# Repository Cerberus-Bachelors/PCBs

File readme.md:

# Interface PCBs 

This repository contains the schematics and pcb designs for the PSU interface and the sensor board interface.

## Buck Boost Interface

This interface adds connectors for buck and boost converters for ease of use.

Buck converter used: LM2596S

Boost converter used: XL6009E1

## Sensor Mount

This interface add connectors for sensor boards, esp and external sensors for ease of use.

IMU Used: Sparkfun ISM330DHCX with MMC5983MA 9Dof board

GNSS Used: NEO-M9N Sparkfun board

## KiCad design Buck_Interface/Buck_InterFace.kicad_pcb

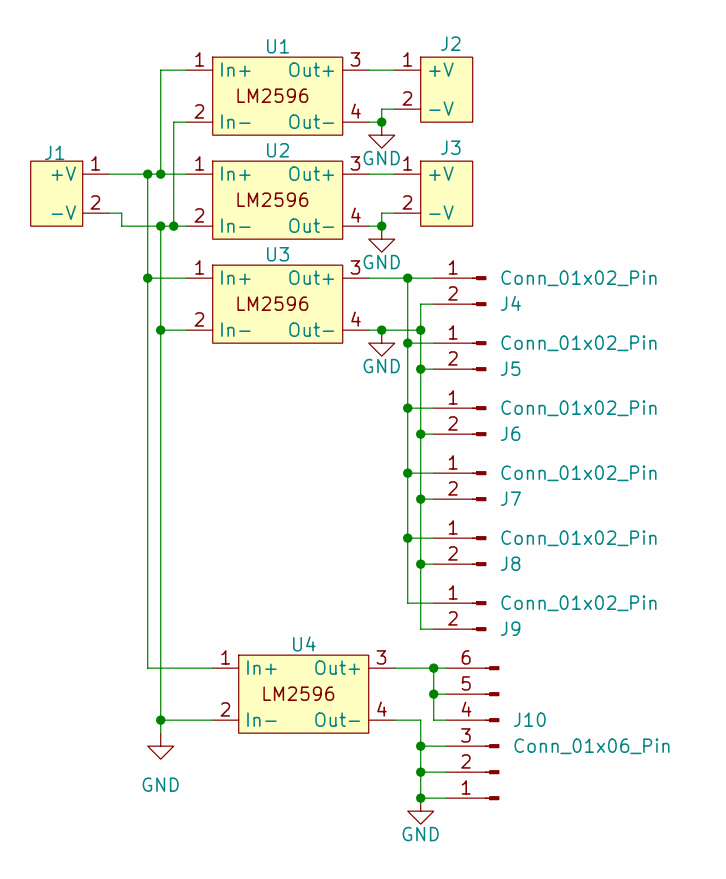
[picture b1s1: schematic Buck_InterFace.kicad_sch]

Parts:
J1, J2, J3: XT30
J4, J5, J6, J7, J8, J9: Conn_01x02_Pin; PinHeader_1x02_P2.54mm_Vertical
J10: Conn_01x06_Pin; PinSocket_1x06_P2.54mm_Vertical
U1, U2, U3, U4: Buck

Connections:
GND: J1.2 (-V), J2.2 (-V), J3.2 (-V), J4.2, J5.2, J6.2, J7.2, J8.2, J9.2, J10.1, J10.2, J10.3, U1.2 (In-), U1.4 (Out-), U2.2 (In-), U2.4 (Out-), U3.2 (In-), U3.4 (Out-), U4.2 (In-), U4.4 (Out-)
unnamed: J1.1 (+V), U1.1 (In+), U2.1 (In+), U3.1 (In+), U4.1 (In+)
unnamed: J2.1 (+V), U1.3 (Out+)
unnamed: J3.1 (+V), U2.3 (Out+)
unnamed: J4.1, J5.1, J6.1, J7.1, J8.1, J9.1, U3.3 (Out+)
unnamed: J10.4, J10.5, J10.6, U4.3 (Out+)

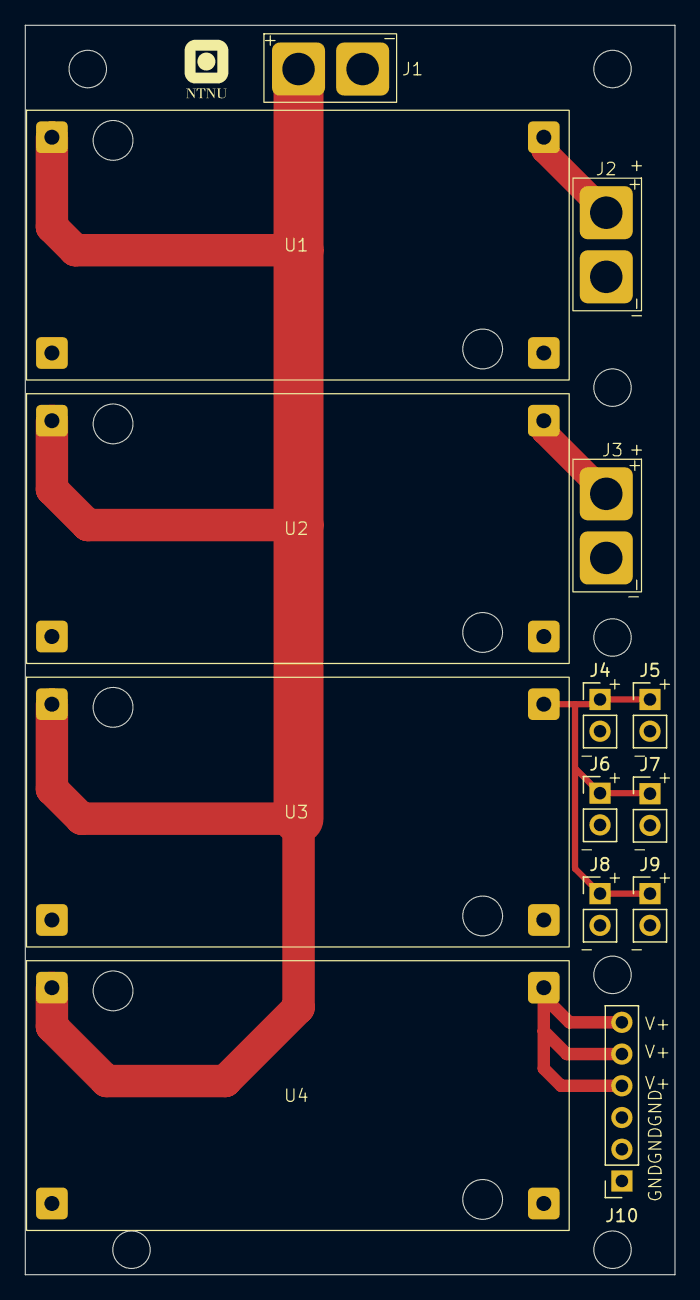
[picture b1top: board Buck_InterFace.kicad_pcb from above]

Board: 2 copper layers, 52.0 x 100.0 mm, 14 parts (0 on the bottom side), 6 nets.

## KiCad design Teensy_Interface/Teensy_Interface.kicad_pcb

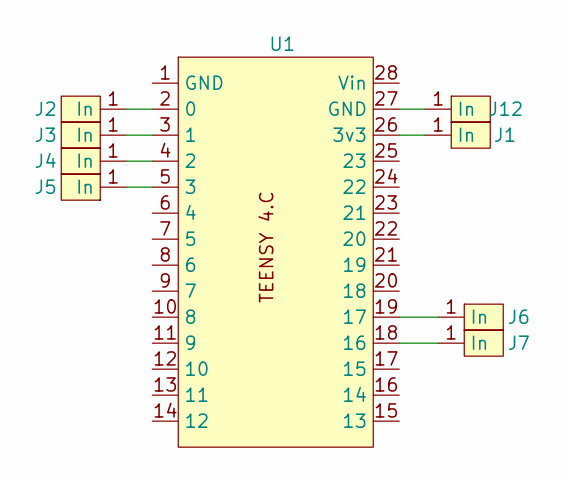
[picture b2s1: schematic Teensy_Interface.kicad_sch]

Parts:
J1, J2, J3, J4, J5, J6, J7, J12: Lug_Terminal
U1: Teensy_14pin

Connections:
unnamed: J1.1 (In), U1.26 (3v3)
unnamed: J2.1 (In), U1.2 (0)
unnamed: J3.1 (In), U1.3 (1)
unnamed: J4.1 (In), U1.4 (2)
unnamed: J5.1 (In), U1.5 (3)
unnamed: J6.1 (In), U1.19 (17)
unnamed: J7.1 (In), U1.18 (16)
unnamed: J12.1 (In), U1.27 (GND)

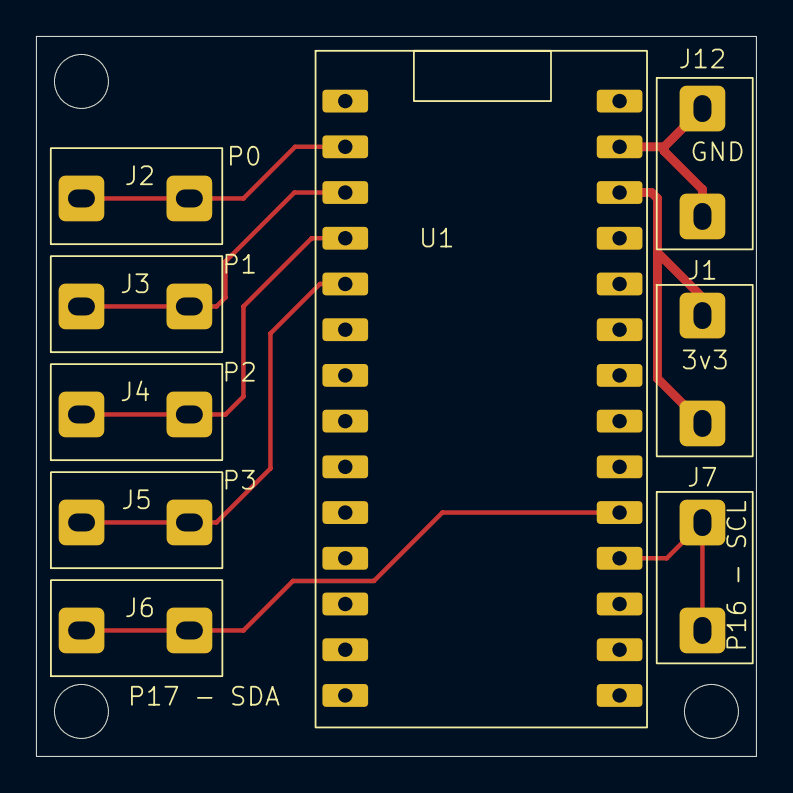
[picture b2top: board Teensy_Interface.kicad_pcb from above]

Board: 2 copper layers, 40.0 x 40.0 mm, 9 parts (0 on the bottom side), 8 nets.

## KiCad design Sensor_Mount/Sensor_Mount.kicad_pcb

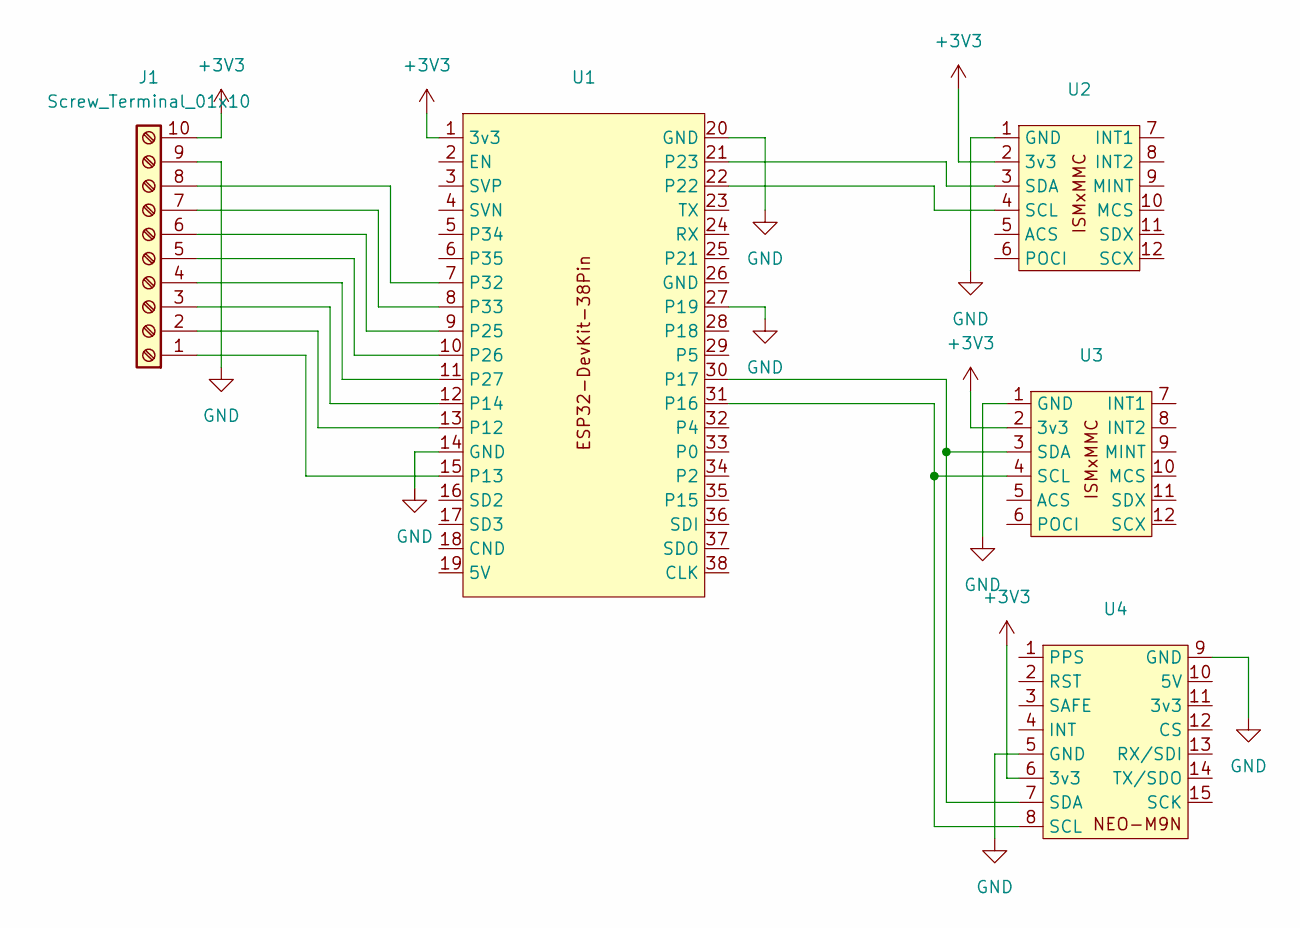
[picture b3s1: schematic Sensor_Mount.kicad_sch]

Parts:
J1: Screw_Terminal_01x10; TerminalBlock_RND_205-00240_1x10_P5.08mm_Horizontal
U1: ESP32-DevKit-GPIO38
U2, U3: ISMxMMC
U4: NEO-M9N

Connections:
+3V3: J1.10, U1.1 (3v3), U2.2 (3v3), U3.2 (3v3), U4.6 (3v3)
GND: J1.9, U1.14 (GND), U1.20 (GND), U1.27 (P19), U2.1 (GND), U3.1 (GND), U4.5 (GND), U4.9 (GND)
unnamed: J1.1, U1.15 (P13)
unnamed: J1.2, U1.13 (P12)
unnamed: J1.3, U1.12 (P14)
unnamed: J1.4, U1.11 (P27)
unnamed: J1.5, U1.10 (P26)
unnamed: J1.6, U1.9 (P25)
unnamed: J1.7, U1.8 (P33)
unnamed: J1.8, U1.7 (P32)
unnamed: U1.31 (P16), U3.4 (SCL), U4.8 (SCL)
unnamed: U1.30 (P17), U3.3 (SDA), U4.7 (SDA)
unnamed: U1.22, U2.4 (SCL)
unnamed: U1.21 (P23), U2.3 (SDA)

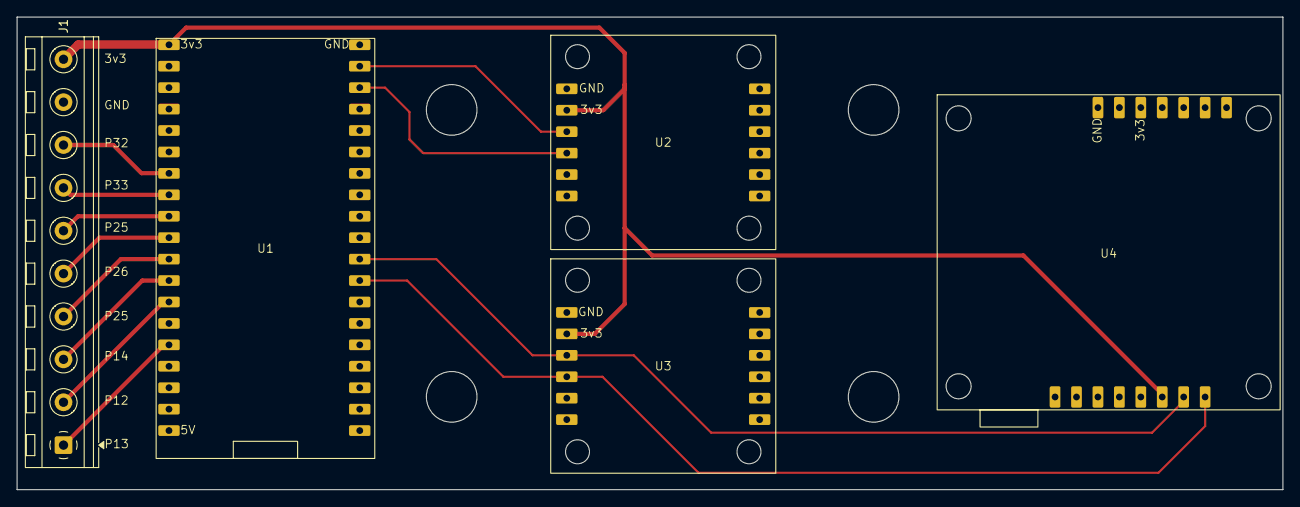
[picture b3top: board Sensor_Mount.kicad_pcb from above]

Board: 2 copper layers, 150.0 x 56.0 mm, 5 parts (0 on the bottom side), 14 nets.

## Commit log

2025-04-01 PCB finnished
2025-04-01 Ordered Parts
2025-04-02 Finnished Teensy and BuckConverter Interface
2025-04-09 added step files
2025-05-20 removed unused stuff
2025-05-20 added readme
